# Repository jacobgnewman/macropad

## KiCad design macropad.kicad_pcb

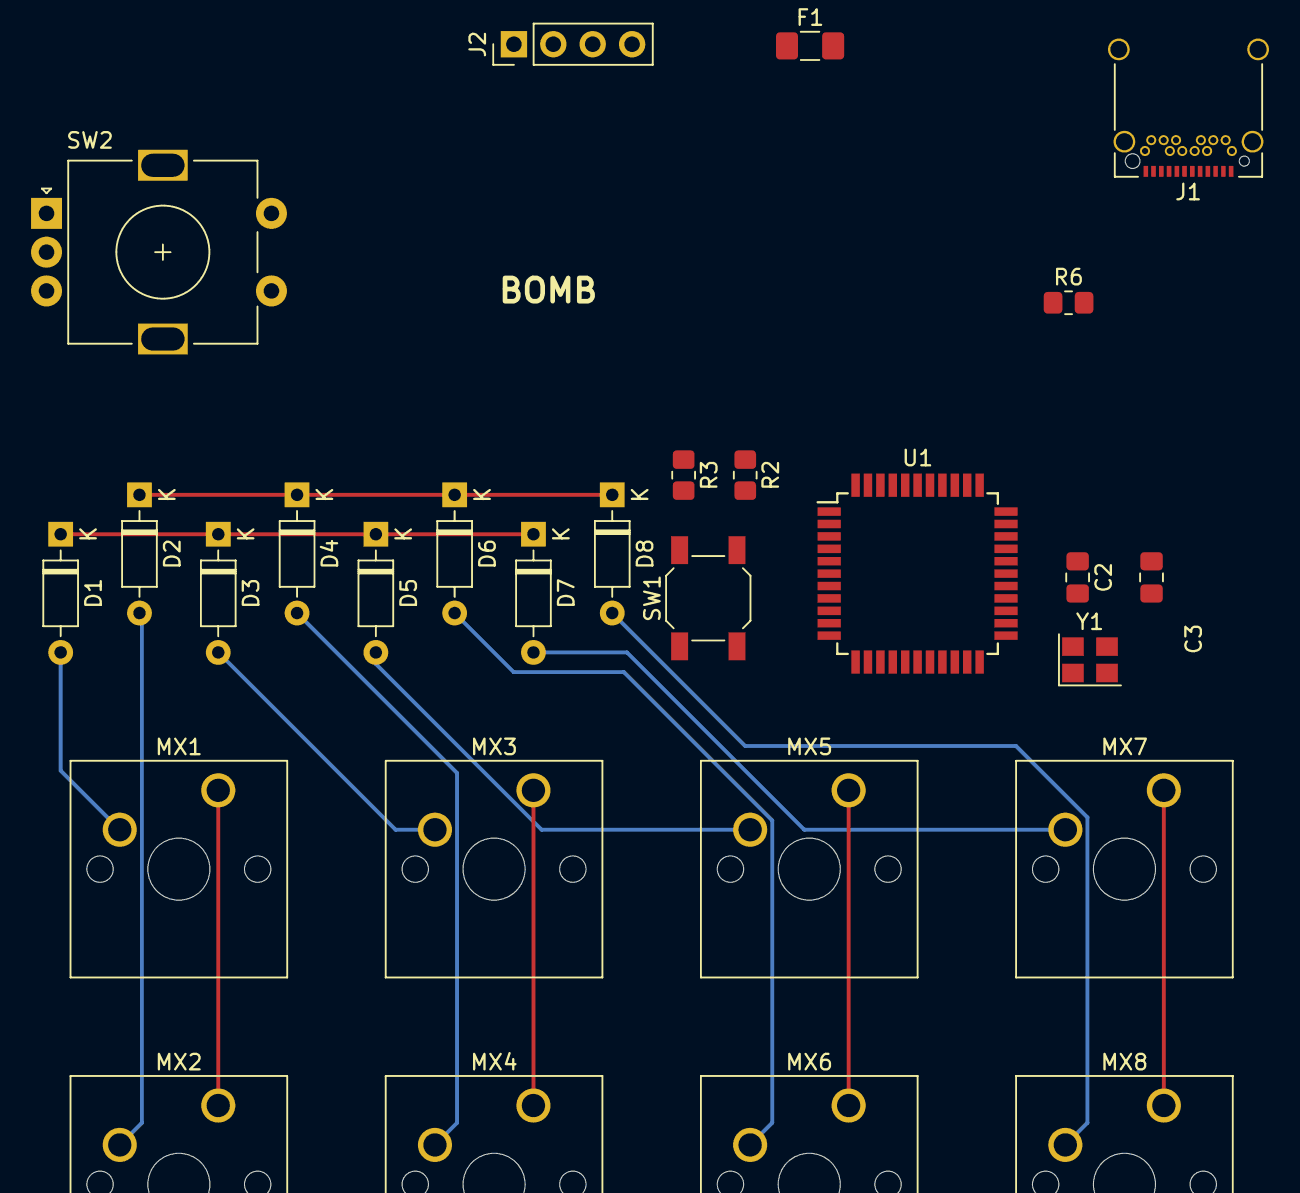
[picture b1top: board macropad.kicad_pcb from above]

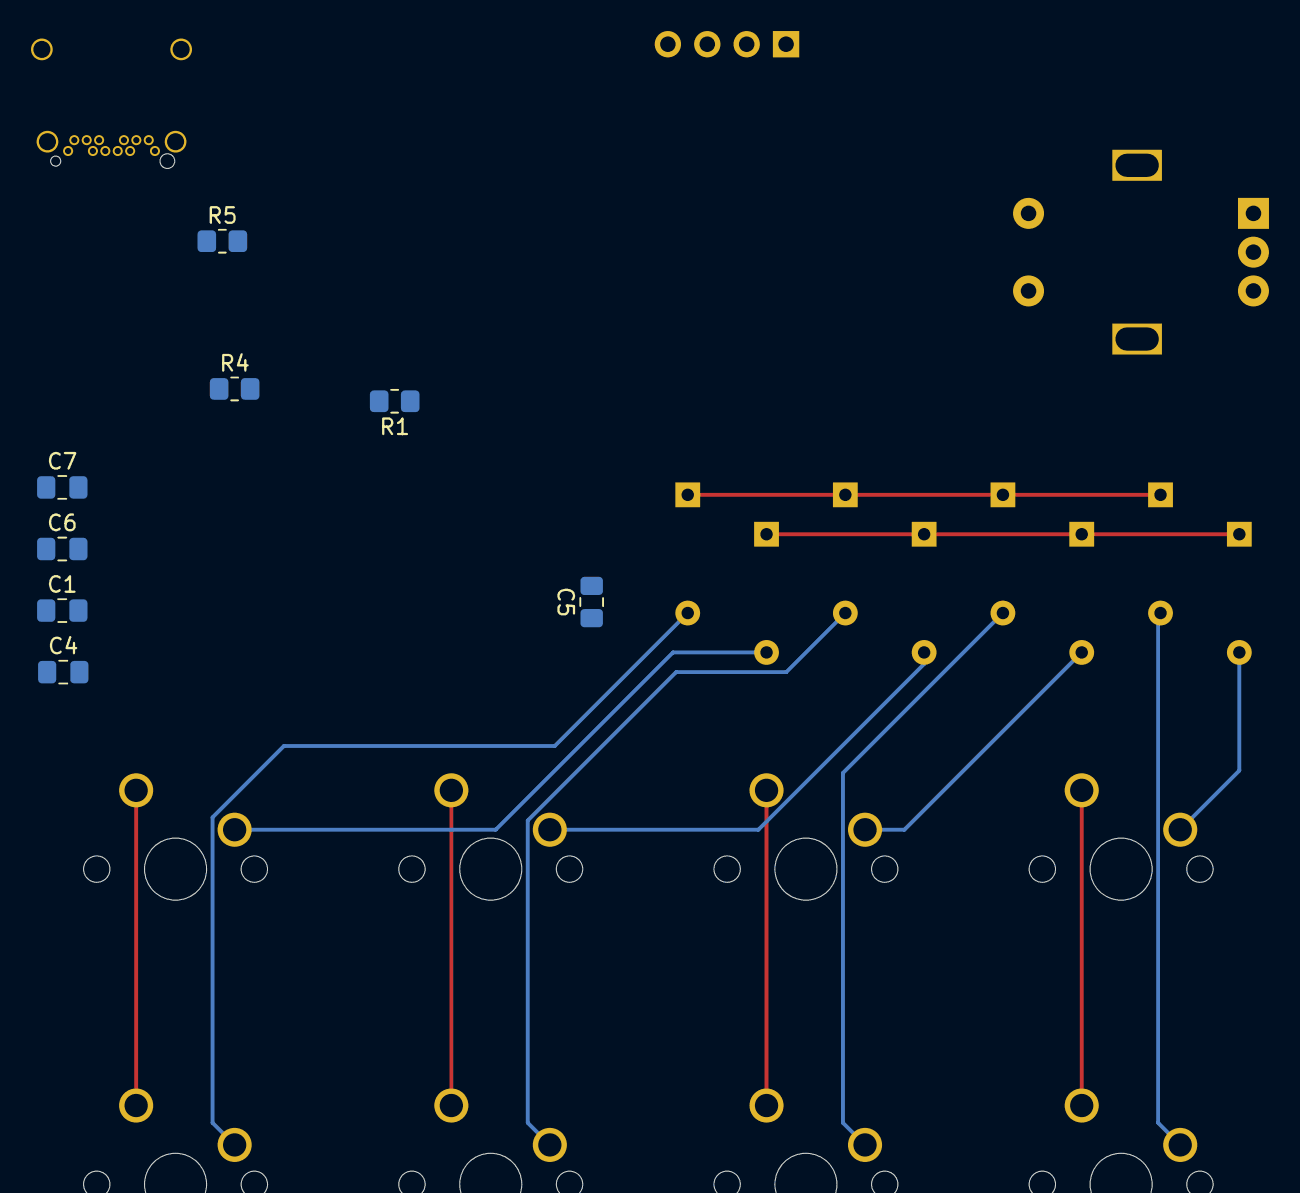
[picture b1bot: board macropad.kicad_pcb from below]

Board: 2 copper layers, 36 parts (8 on the bottom side), 28 nets.

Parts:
C1, C4, C6: 0.1uf; C_0805_2012Metric_Pad1.18x1.45mm_HandSolder
C2, C3: 22pF; C_0805_2012Metric_Pad1.18x1.45mm_HandSolder
C5: 1uf; C_0805_2012Metric_Pad1.18x1.45mm_HandSolder
C7: 10uf; C_0805_2012Metric_Pad1.18x1.45mm_HandSolder
D1, D2, D3, D4, D5, D6, D7, D8: 1N4148; D_DO-35_SOD27_P7.62mm_Horizontal
F1: 500mA; Fuse_1206_3216Metric_Pad1.42x1.75mm_HandSolder
J1: USB_C_Receptacle_USB2.0; USB_C_Receptacle_Amphenol_12401548E4-2A_CircularHoles
J2: Conn_01x04; PinHeader_1x04_P2.54mm_Vertical
MX1, MX2, MX3, MX4, MX5, MX6, MX7, MX8: MX-NoLED; SW_Cherry_MX_1.00u_PCB
R1, R2: 22; R_0805_2012Metric_Pad1.20x1.40mm_HandSolder
R3, R4: 10k; R_0805_2012Metric_Pad1.20x1.40mm_HandSolder
R5, R6: 5.1k; R_0805_2012Metric_Pad1.20x1.40mm_HandSolder
SW1: SW_Push; SW_SPST_SKQG_WithStem
SW2: RotaryEncoder_Switch; RotaryEncoder_Alps_EC11E-Switch_Vertical_H20mm
U1: ATmega32U4-A; TQFP-44_10x10mm_P0.8mm
Y1: 16MHz; Crystal_SMD_3225-4Pin_3.2x2.5mm

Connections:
+5V: C1.1, C4.1, C6.1, C7.1, F1.2, J2.2, R3.1, U1.2 (UVCC), U1.7 (VBUS), U1.14 (VCC), U1.24 (AVCC), U1.34 (VCC), U1.44 (AVCC)
COL0: MX1.1 (COL), MX2.1 (COL)
COL1: MX3.1 (COL), MX4.1 (COL)
COL2: MX5.1 (COL), MX6.1 (COL)
COL3: MX7.1 (COL), MX8.1 (COL)
D+: J1.A6 (D+), J1.B6 (D+), R2.1
D-: J1.A7 (D-), J1.B7 (D-), R1.2
GND: C1.2, C2.1, C3.1, C4.2, C5.2, C6.2, C7.2, J1.A1 (GND), J1.A12 (GND), J1.B1 (GND), J1.B12 (GND), J1.S1 (SHIELD), J2.1, R4.2, R5.2, R6.2, SW1.1, SW2.C, U1.5 (UGND), U1.15 (GND), U1.23 (GND), U1.35 (GND), U1.43 (GND), Y1.2, Y1.4
unnamed: C2.2, U1.17 (XTAL1), Y1.1
unnamed: C3.2, U1.16 (XTAL2), Y1.3
unnamed: C5.1, U1.6 (UCAP)
unnamed: D1.2 (A), MX1.2 (ROW)
unnamed: D2.2 (A), MX2.2 (ROW)
unnamed: D3.2 (A), MX3.2 (ROW)
unnamed: D4.2 (A), MX4.2 (ROW)
unnamed: D5.2 (A), MX5.2 (ROW)
unnamed: D6.2 (A), MX6.2 (ROW)
unnamed: D7.2 (A), MX7.2 (ROW)
unnamed: D8.2 (A), MX8.2 (ROW)
unnamed: J1.A5 (CC1), R6.1
unnamed: J1.B5 (CC2), R5.1
unnamed: R1.1, U1.3 (D-)
unnamed: R2.2, U1.4 (D+)
unnamed: R3.2, SW1.2, U1.13 (~RESET)
unnamed: R4.1, U1.33 (~HWB/PE2)
ROW0: D1.1 (K), D3.1 (K), D5.1 (K), D7.1 (K)
ROW1: D2.1 (K), D4.1 (K), D6.1 (K), D8.1 (K)
VCC: F1.1, J1.A4 (VBUS), J1.A9 (VBUS), J1.B4 (VBUS), J1.B9 (VBUS)

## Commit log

2022-04-01 Adding the initial kicad files + plate svg
2022-04-01 Add switch library submodules
2022-04-02 schematic added
2022-04-04 Added rotary encoder and pins for screen
